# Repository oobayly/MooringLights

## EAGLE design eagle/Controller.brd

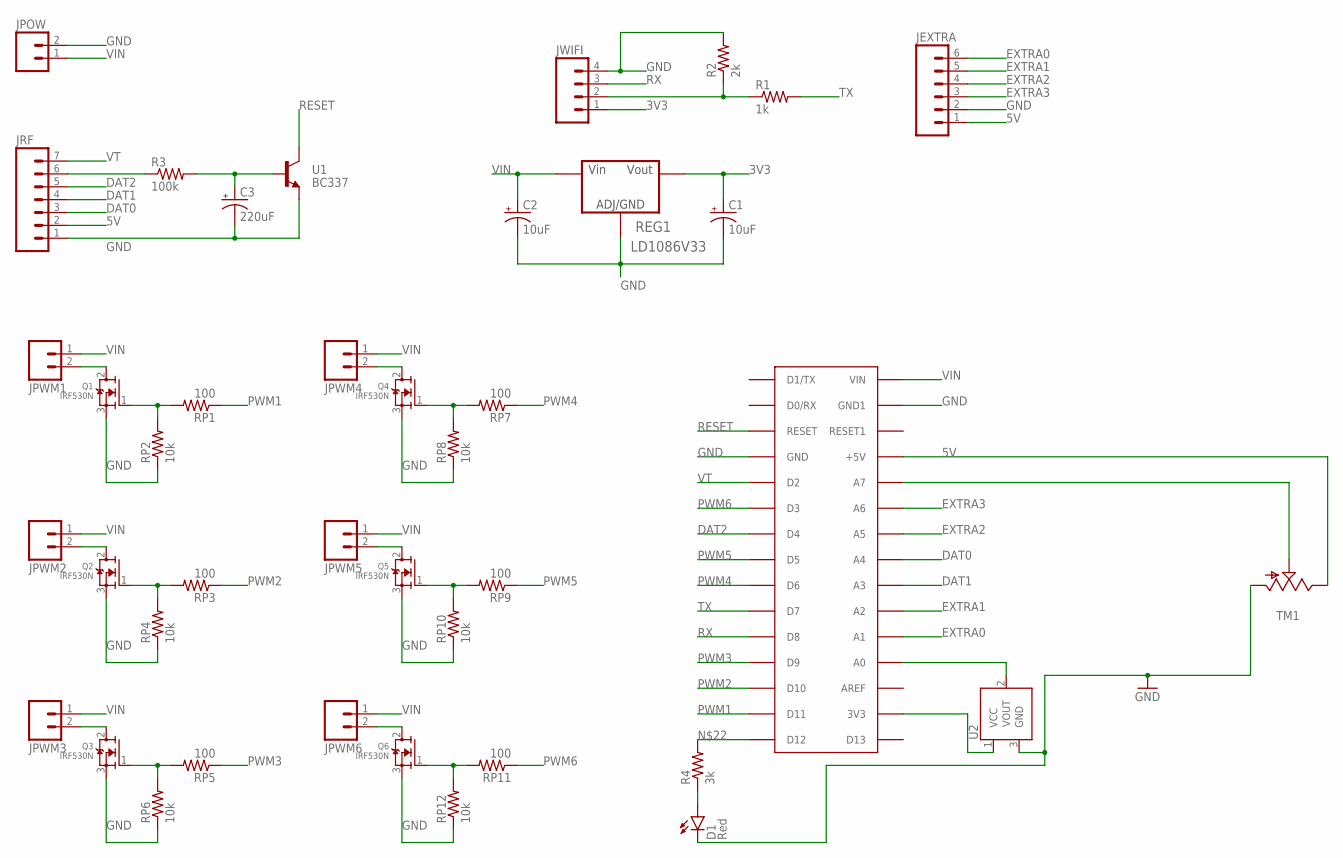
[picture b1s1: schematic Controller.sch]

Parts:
C1, C2: 10uF; CPOL-RADIAL-10UF-25V
C3: 220uF; CPOL-RADIAL-100UF-25V
D1: Red; LED5MM
JEXTRA: M06SILK_FEMALE_PTH; 1X06
JPOW: M025MM; SCREWTERMINAL-5MM-2
JPWM1, JPWM2, JPWM3, JPWM4, JPWM5, JPWM6: M025MM; SCREWTERMINAL-5MM-2
JRF: M07; 1X07
JWIFI: M04PTH; 1X04
NANO: ARDUINONANONO-MOUNT; PDIP-32-NO-MOUNT
Q1, Q2, Q3, Q4, Q5, Q6: IRF530N; TO220V
R1: 1k; AXIAL-0.4
R2: 2k; AXIAL-0.4
R3: 100k; AXIAL-0.4
R4: 3k; AXIAL-0.4
REG1: LD1086V33; TO254P482X1024X3124-3P
RP1, RP3, RP5, RP7, RP9, RP11: 100; AXIAL-0.4
RP2, RP4, RP6, RP8, RP10, RP12: 10k; AXIAL-0.4
TM1: TRIM; 6MM
U1: BC337; TO-92
U2: TMP36GT9; TO-92

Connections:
3V3: C1.1 (+), JWIFI.1, REG1.2 (VOUT)
5V: JEXTRA.1, JRF.2, NANO.+5V, TM1.E
DAT0: JRF.3, NANO.A3 (A4)
DAT1: JRF.4, NANO.A4 (A3)
DAT2: JRF.5, NANO.D4
EXTRA0: JEXTRA.6, NANO.A6 (A1)
EXTRA1: JEXTRA.5, NANO.A5 (A2)
EXTRA2: JEXTRA.4, NANO.A2 (A5)
EXTRA3: JEXTRA.3, NANO.A1 (A6)
GND: C1.2 (-), C2.2 (-), C3.2 (-), D1.K (C), JEXTRA.2, JPOW.2, JRF.1, JWIFI.4, NANO.GND, NANO.GND1, Q1.3 (S), Q2.3 (S), Q3.3 (S), Q4.3 (S), Q5.3 (S), Q6.3 (S), R2.P$2 (2), REG1.1 (ADJ/GND), RP2.P$1 (1), RP4.P$1 (1), RP6.P$1 (1), RP8.P$1 (1), RP10.P$1 (1), RP12.P$1 (1), TM1.A, U1.3 (E), U2.3 (GND)
unnamed: NANO.A0 (A7), TM1.S
unnamed: JWIFI.2, R1.P$1 (1), R2.P$1 (1)
unnamed: JRF.6, R3.P$1 (1)
unnamed: C3.1 (+), R3.P$2 (2), U1.2 (B)
unnamed: Q1.1 (G), RP1.P$2 (2), RP2.P$2 (2)
unnamed: JPWM1.2, Q1.2 (D)
unnamed: Q2.1 (G), RP3.P$2 (2), RP4.P$2 (2)
unnamed: D1.A, R4.P$1 (1)
unnamed: Q3.1 (G), RP5.P$2 (2), RP6.P$2 (2)
unnamed: JPWM3.2, Q3.2 (D)
unnamed: Q4.1 (G), RP7.P$2 (2), RP8.P$2 (2)
unnamed: JPWM4.2, Q4.2 (D)
unnamed: Q5.1 (G), RP9.P$2 (2), RP10.P$2 (2)
unnamed: JPWM5.2, Q5.2 (D)
unnamed: Q6.1 (G), RP11.P$2 (2), RP12.P$2 (2)
unnamed: JPWM6.2, Q6.2 (D)
unnamed: JPWM2.2, Q2.2 (D)
unnamed: NANO.A7 (A0), U2.2 (VOUT)
unnamed: NANO.D12, R4.P$2 (2)
unnamed: NANO.3V3, U2.1 (VCC)
PWM1: NANO.D11, RP1.P$1 (1)
PWM2: NANO.D10, RP3.P$1 (1)
PWM3: NANO.D9, RP5.P$1 (1)
PWM4: NANO.D6, RP7.P$1 (1)
PWM5: NANO.D5, RP9.P$1 (1)
PWM6: NANO.D3, RP11.P$1 (1)
RESET: NANO.RESET, U1.1 (C)
RX: JWIFI.3, NANO.D8
TX: NANO.D7, R1.P$2 (2)
VIN: C2.1 (+), JPOW.1, JPWM1.1, JPWM2.1, JPWM3.1, JPWM4.1, JPWM5.1, JPWM6.1, NANO.VIN, REG1.3 (VIN)
VT: JRF.7, NANO.D2

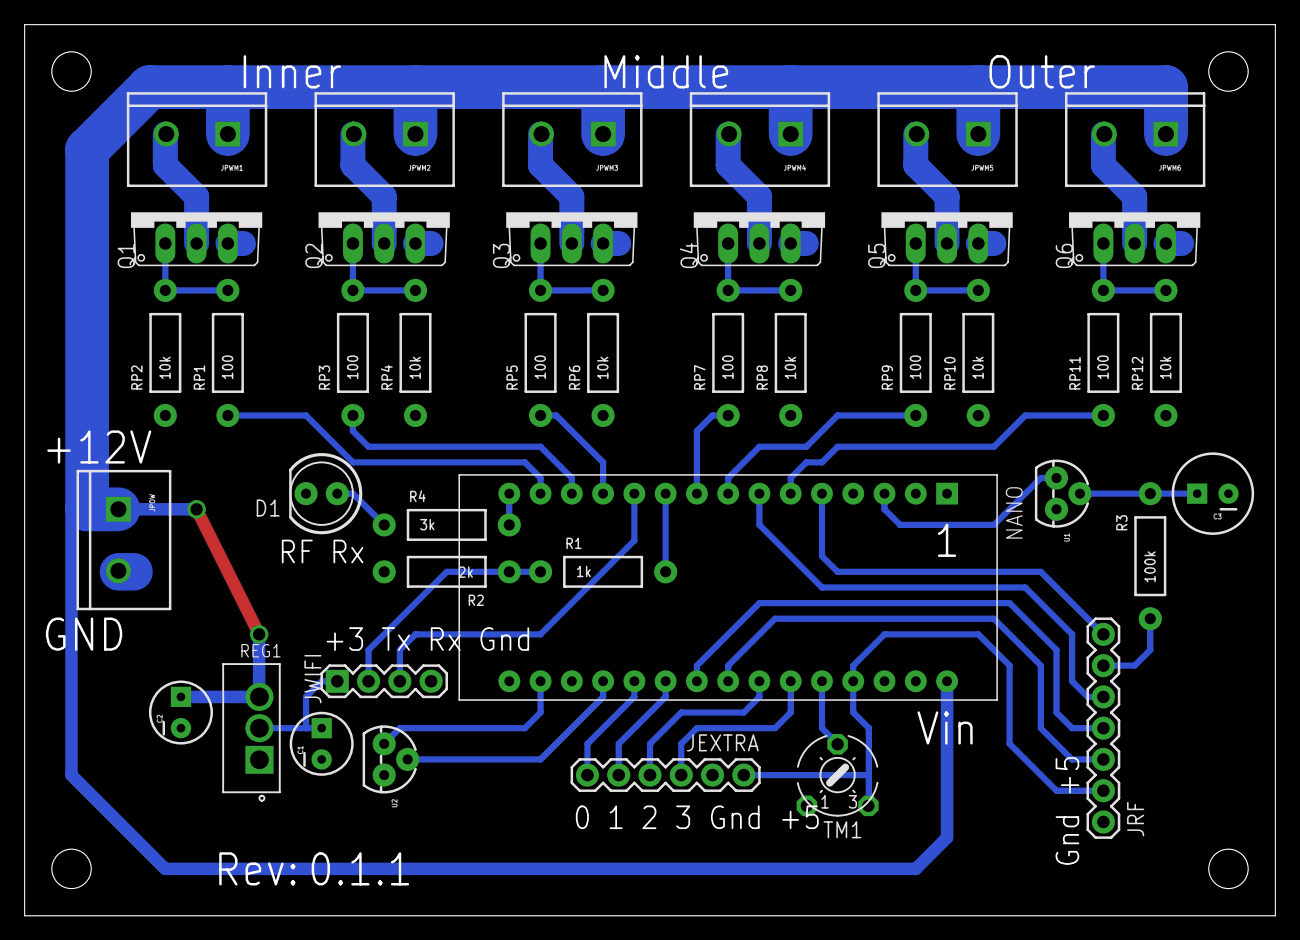
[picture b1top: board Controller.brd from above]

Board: 2 copper layers, 101.6 x 72.4 mm, 41 parts (0 on the bottom side), 41 nets.

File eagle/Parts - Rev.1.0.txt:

Partlist

Exported from Controller.brd at 20/05/2016 10:56

EAGLE Version 7.5.0 Copyright (c) 1988-2015 CadSoft

Assembly variant: 

Part     Value          Package                Library               Position (mm)         Orientation

C1       10uF           CPOL-RADIAL-10UF-25V   SparkFun-Capacitors   (24.13 13.97)         R90
C2       10uF           CPOL-RADIAL-10UF-25V   SparkFun-Capacitors   (12.7 16.51)          R90
C3       100uF          CPOL-RADIAL-100UF-25V  SparkFun-Capacitors   (96.52 34.29)         R180
D1       Red            LED5MM                 SparkFun-LED          (24.13 34.29)         R180
JEXTRA                  1X06                   SparkFun-Connectors   (58.42 11.43)         R180
JPOW                    SCREWTERMINAL-5MM-2    SparkFun-Connectors   (7.62 33.02)          R270
JPWM1                   SCREWTERMINAL-5MM-2    SparkFun-Connectors   (16.51 63.5)          R180
JPWM2                   SCREWTERMINAL-5MM-2    SparkFun-Connectors   (31.75 63.5)          R180
JPWM3                   SCREWTERMINAL-5MM-2    SparkFun-Connectors   (46.99 63.5)          R180
JPWM4                   SCREWTERMINAL-5MM-2    SparkFun-Connectors   (62.23 63.5)          R180
JPWM5                   SCREWTERMINAL-5MM-2    SparkFun-Connectors   (77.47 63.5)          R180
JPWM6                   SCREWTERMINAL-5MM-2    SparkFun-Connectors   (92.71 63.5)          R180
JRF                     1X07                   SparkFun-Connectors   (87.63 7.62)          R90
JWIFI                   1X04                   SparkFun-Connectors   (25.4 19.05)          R0
NANO                    PDIP-32-NO-MOUNT       jet-lib               (77.47 34.29)         R270
Q1       IRF530N        TO220V                 adafruit              (13.97 57.15)         R0
Q2       IRF530N        TO220V                 adafruit              (29.21 57.15)         R0
Q3       IRF530N        TO220V                 adafruit              (44.45 57.15)         R0
Q4       IRF530N        TO220V                 adafruit              (59.69 57.15)         R0
Q5       IRF530N        TO220V                 adafruit              (74.93 57.15)         R0
Q6       IRF530N        TO220V                 adafruit              (90.17 57.15)         R0
R1       1k             AXIAL-0.4              SparkFun-Passives     (46.99 27.94)         R0
R2       2k             AXIAL-0.4              SparkFun-Passives     (34.29 27.94)         R180
R3       220k           AXIAL-0.4              SparkFun-Passives     (91.44 29.21)         R90
R4       3k             AXIAL-0.4              SparkFun-Passives     (34.29 31.75)         R0
REG1     LD1086V33      TO254P482X1024X3124-3P STM-LD1086V33         (17.78 17.78)         R90
RP1      100            AXIAL-0.4              SparkFun-Passives     (16.51 45.72)         R90
RP2      10k            AXIAL-0.4              SparkFun-Passives     (11.43 45.72)         R90
RP3      100            AXIAL-0.4              SparkFun-Passives     (26.67 45.72)         R90
RP4      10k            AXIAL-0.4              SparkFun-Passives     (31.75 45.72)         R90
RP5      100            AXIAL-0.4              SparkFun-Passives     (41.91 45.72)         R90
RP6      10k            AXIAL-0.4              SparkFun-Passives     (46.99 45.72)         R90
RP7      100            AXIAL-0.4              SparkFun-Passives     (57.15 45.72)         R90
RP8      10k            AXIAL-0.4              SparkFun-Passives     (62.23 45.72)         R90
RP9      100            AXIAL-0.4              SparkFun-Passives     (72.39 45.72)         R90
RP10     10k            AXIAL-0.4              SparkFun-Passives     (77.47 45.72)         R90
RP11     100            AXIAL-0.4              SparkFun-Passives     (87.63 45.72)         R90
RP12     10k            AXIAL-0.4              SparkFun-Passives     (92.71 45.72)         R90
TM1                     6MM                    adafruit              (66.04 11.43)         R0
U1       BC337          TO-92                  SparkFun-DiscreteSemi (83.82 34.29)         R270
U2                      TO-92                  SparkFun-Sensors      (29.21 12.7)          R270

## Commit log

2015-07-14 Update WiFi details
2015-11-12 Add instructions for hardware PWM controller
2015-11-12 Reduce intensity of lights during POST
2015-11-12 Add documentation for ESP8266 AT commands
2015-11-13 Use promise for writing the levels
2015-11-13 Move socket into its own factory
2015-11-13 Improve logging for unexpected packets and return the LED status on SET
2015-11-13 Send the correct bytes to the controller
2015-11-13 Update plugins
2015-11-13 Make the case the same in TCPClient
2015-11-13 Use left-hand close button
2015-11-13 Update add icon
2015-11-17 Update phonegap plugins
2015-11-17 Hacky workaround - restart the TCP server every 5 minutes
2015-11-17 Update phonegap plugins, again
2015-11-17 Attempt to reconnect to the Wifi every minute if there is an error
2015-11-17 Move restart server commands to main loop
2015-11-17 Use getMUX to test if the board has been reset
2015-11-17 Move reset wifi to main loop
2016-05-18 Updated for new version of the controller
2016-05-18 Add Eagle CAD project
2016-05-18 Fix command structure and allow the controller to close the connection
2016-05-18 Fix incorrect PWM initialisation and Timer1 duty cycle shift
2016-05-18 Revert to 1ms timer for pwm frequency and only trigger every TIMER1_INTERVAL
2016-05-19 Make struct references volatile
2016-05-19 Increase number of settings per chaser
2016-05-19 Update board
    Remove 2 trim pots and replace with EXTRA2/3
    Increase size of vias
    Increase border of board
    Improve labeling
2016-05-20 Updated BOM
2016-05-20 Add Revision to board
2016-05-23 Add more text labels
2016-05-23 Add constant attributes
2016-05-23 Add READ and WRITE chaser commands
2016-05-23 Add default defines in case passwords.h is not present
2016-05-23 Rename chaser to scene
2016-05-23 Mirroring of scene is done in via the controller
2016-05-23 Create default scenes
2016-05-23 Get rid of the radio button list due to delay bug in chrome
    See https://forum.ionicframework.com/t/bug-unwanted-delay-in-updating-ng-repeat-a-populated-with-ion-radio/2275/3
2016-05-23 Updated defines for Trimpots and Extra
2016-05-23 Add intensity limiting using the trimpot
2016-05-23 Add intensity compression
2016-05-23 Move options to popover and add temperature information
2016-05-24 Add persistent configuration struct
2016-05-24 Add options for setting the fade and sleep intervals
2016-05-24 Implement TCPClient timeout
2016-05-24 Make sure the connection isn't closed prematurely
2016-05-24 Improve notifications
2016-05-24 Fix endianess
2016-05-24 Remove rendundent SLEEP mode
2016-05-24 Don't set the levels when the app is run
2016-05-24 Make connection timeout user configurable
2016-05-24 Change popover header colour
2016-05-24 Reorder services
2016-05-24 Add status to options menu
2016-05-24 Hide the popover
2016-05-24 Change title
2016-05-25 Remove stray character
2016-05-25 Add Presets and make controller names and states less ambigious
2016-05-25 Rename files
2016-05-25 Improve UI
2016-05-25 Fix bug with factories using the same DEFAULTS reference
2016-05-25 Initialise Chaser values to zero
2016-05-25 Fix: Copy the actual size of the Chaser struct when READing
2016-05-25 Add Chaser factory
2016-05-25 JSHint tidy up
2016-05-25 Fix: Count parsing
2016-05-25 Prepare files for new directives
2016-05-25 Add chaser editing
2016-05-25 Remove Channel class, and replace with literals.
2016-05-25 Add lights directive
2016-05-25 Require data to be returned by the controller
2016-05-25 Various bug fixes
2016-05-26 Move scene editor to its own directive
2016-05-26 Add scene editing to chaser
2016-05-26 Finish the Chaser page
2016-05-26 Add USE function that takes a Chaser struct
2016-05-26 Don't write chasers to EEPROM every restart
2016-05-26 Fix: Interval not copied from defaults
2016-05-26 Decrease timer tick resolution
    Seems to interfere with Software Serial
2016-05-26 Fix warnings and wrap string in F macro
2016-05-26 Change reset circuit to work with lower Arduino resistor values
2016-05-27 Add poup for writing custom chaser to preset button
2016-05-27 Move all logging and toasts to the scene and chaser factories
2016-05-27 Add scene selector to chaser editor
2016-05-27 Move Fade & Sleep functions to LightService
2016-05-27 General code tidy up
2016-05-27 Move temperature fucntion to LightService
2016-05-27 Add defaults for configuration
2016-06-03 Increase number of scenes available per chaser
2016-06-03 Decrease number of scenes per chaser due to buffer constraints
    Still need to increase the buffer in SoftwareSerial.h:
    http://forum.arduino.cc/index.php?topic=244398.0
2016-06-03 Reduce programs again due to buffer contraints
    Didn't take command into account

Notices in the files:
parts and their libraries:
SparkFun-Connectors: Licensing: Creative Commons ShareAlike 4.0 International - https://creativecommons.org/licenses/by-sa/4.0
